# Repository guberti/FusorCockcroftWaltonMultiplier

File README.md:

## Fusor Cockcroft-Walton Multiplier
For [Eastside Prep's Fusor project](http://www.eastsideprep.org/fusor-project/), we need a high voltage (~40 kV) and moderate current (~10 mA) power supply. This is my design for a [Cockcroft-Walton Multiplier](https://en.wikipedia.org/wiki/Cockcroft%E2%80%93Walton_generator) to fulfill those requirements.

While we originally bought a Cockcroft-Walton multiplier off Ebay for $100, we found that while it generated very high voltages (~150 kV) it collapsed under virtually any load (~100 µA). This is likely because it used small 22 pF capacitors. Since the circuit design for a CW multiplier is so simple, I opted to simply get new circuit boards made instead of trying to resolder new capacitors onto the exising boards.

The boards were designed using EAGLE and manufactured by JLBPCB. The capacitors and diodes were purchased off Ebay. The boards are designed to be given an input voltage of 15 kV AC (the output of a neon sign transformer), but they should work for any voltage.

This Github repo consists exclusively of the EAGLE files used to design these boards. 

*The manufactured but unsoldered circuit boards*

*The layout of the circuit boards in EAGLE*

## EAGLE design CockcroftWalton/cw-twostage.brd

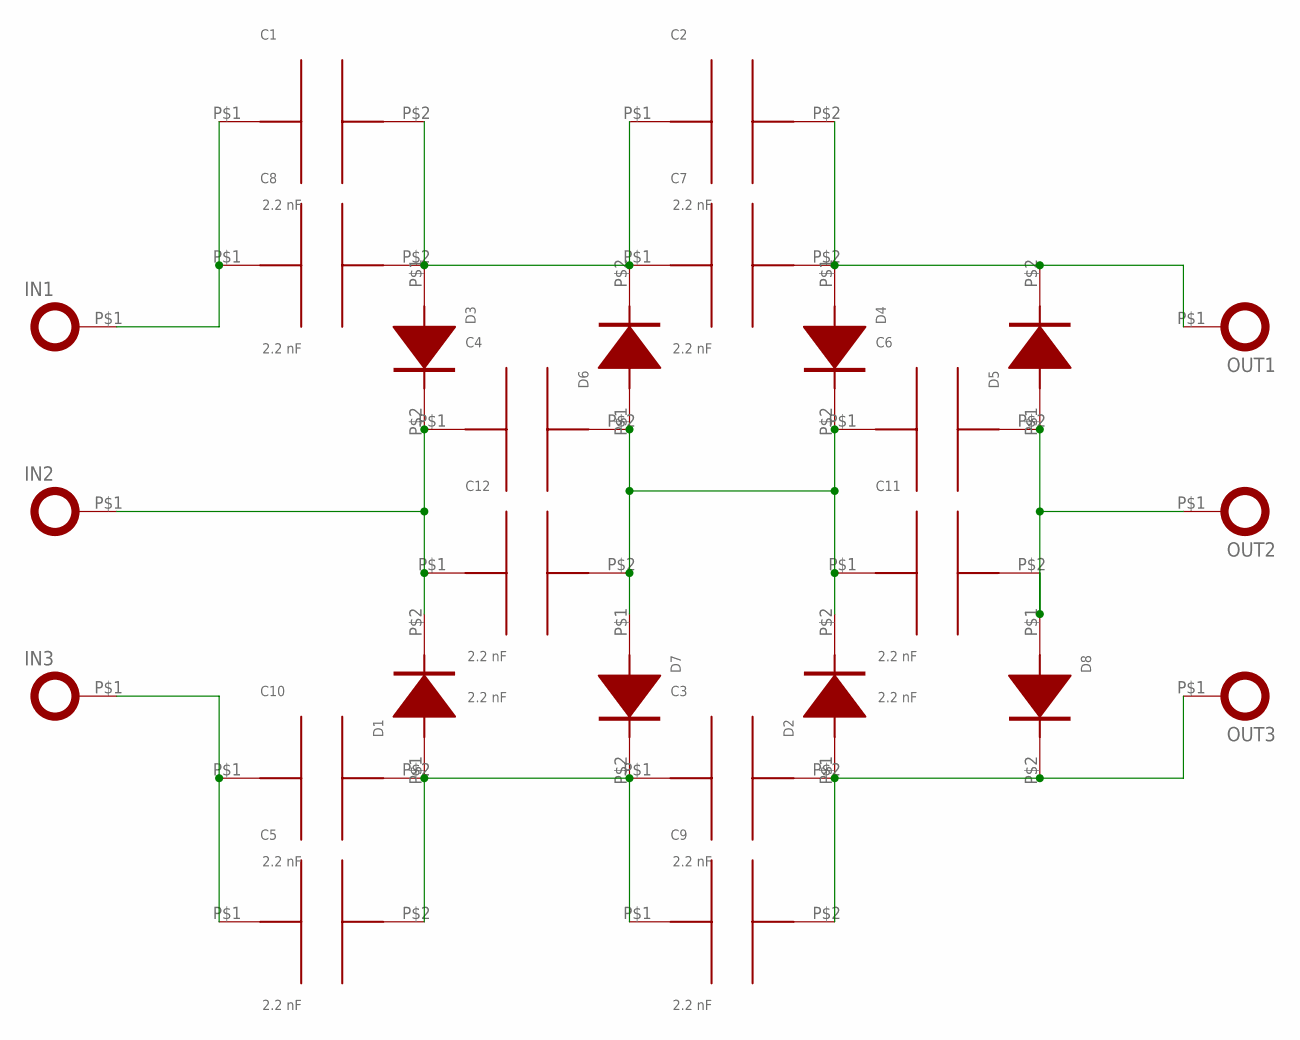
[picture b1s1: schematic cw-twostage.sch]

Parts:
C1, C2, C3, C4, C5, C6, C7, C8, C9, C10, C11, C12: 2.2 nF; CAP_CT81_12
D1, D2, D3, D4, D5, D6, D7, D8: DIODE_14MM; DIODE_14
IN1, IN2, IN3: TERMINAL_M6; LUG_SQUARE_M6
OUT1, OUT2, OUT3: TERMINAL_M6; LUG_SQUARE_M6

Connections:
unnamed: C5.P$1, C10.P$1, IN3.P$1
unnamed: C4.P$2, C6.P$1, C11.P$1, C12.P$2, D2.P$2 (CATHODE), D4.P$2 (CATHODE), D6.P$1 (ANODE), D7.P$1 (ANODE)
unnamed: C1.P$1, C8.P$1, IN1.P$1
unnamed: C6.P$2, C11.P$2, D5.P$1 (ANODE), D8.P$1 (ANODE), OUT2.P$1
unnamed: C3.P$1, C5.P$2, C9.P$1, C10.P$2, D1.P$1 (ANODE), D7.P$2 (CATHODE)
unnamed: C1.P$2, C2.P$1, C7.P$1, C8.P$2, D3.P$1 (ANODE), D6.P$2 (CATHODE)
unnamed: C3.P$2, C9.P$2, D2.P$1 (ANODE), D8.P$2 (CATHODE), OUT3.P$1
unnamed: C4.P$1, C12.P$1, D1.P$2 (CATHODE), D3.P$2 (CATHODE), IN2.P$1
unnamed: C2.P$2, C7.P$2, D4.P$1 (ANODE), D5.P$2 (CATHODE), OUT1.P$1

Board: 2 copper layers, 26 parts (2 on the bottom side), 9 nets, no tracks yet.

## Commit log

2019-07-03 File dump
2019-07-03 Move EAGLE files to own folder to make README more visible
